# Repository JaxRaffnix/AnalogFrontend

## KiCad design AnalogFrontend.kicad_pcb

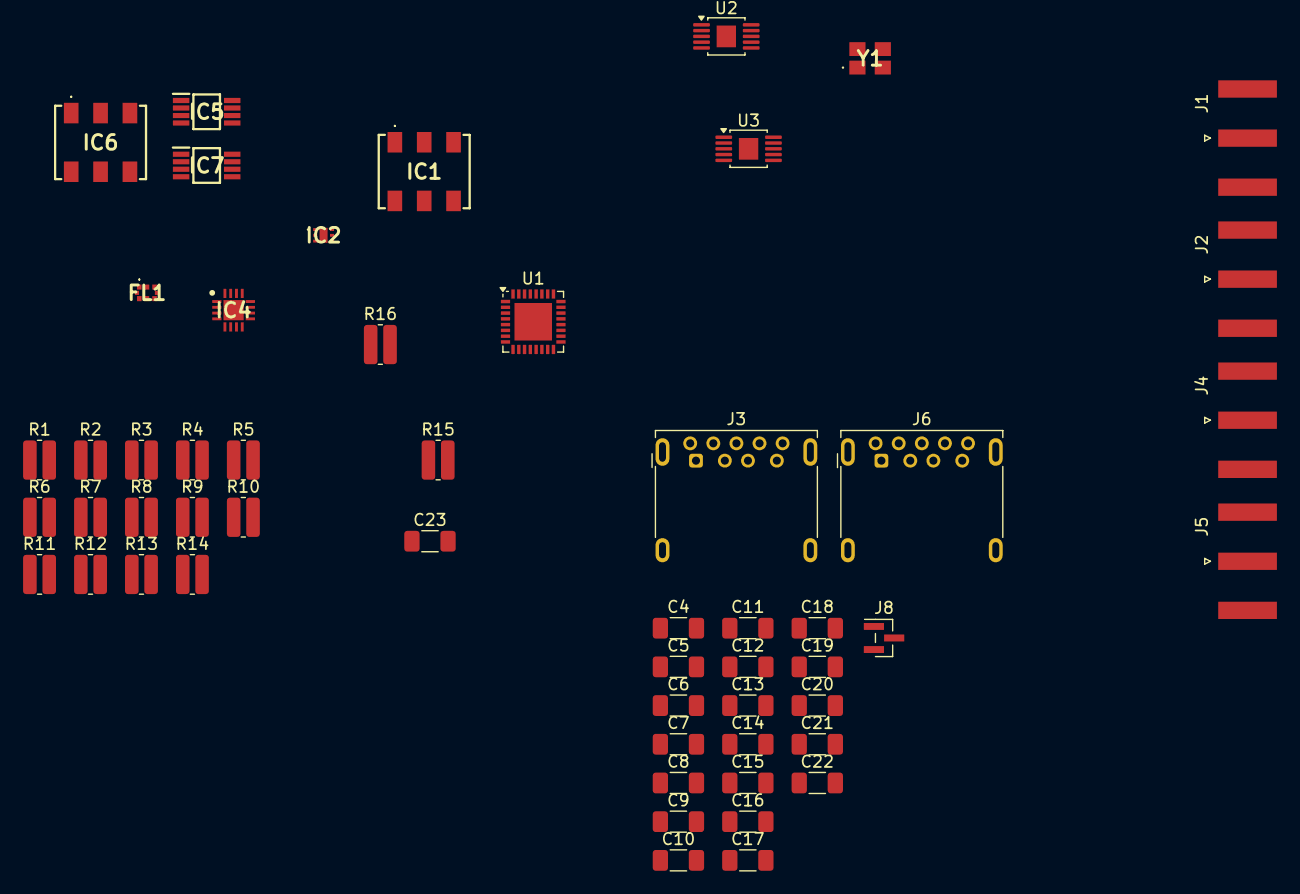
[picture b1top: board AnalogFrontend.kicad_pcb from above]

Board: 2 copper layers, 54 parts (0 on the bottom side), 33 nets, no tracks yet.

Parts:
C4, C5, C6, C21, C22, C23: 4.7muF; C_1206_3216Metric_Pad1.33x1.80mm_HandSolder
C7, C10, C12: 10pF; C_1206_3216Metric_Pad1.33x1.80mm_HandSolder
C8, C9, C11: 0.1muF; C_1206_3216Metric_Pad1.33x1.80mm_HandSolder
C13: 2.7mu; C_1206_3216Metric_Pad1.33x1.80mm_HandSolder
C14: 39n; C_1206_3216Metric_Pad1.33x1.80mm_HandSolder
C15: 1.2mu; C_1206_3216Metric_Pad1.33x1.80mm_HandSolder
C16, C17, C18, C19: 1n; C_1206_3216Metric_Pad1.33x1.80mm_HandSolder
C20: 10n; C_1206_3216Metric_Pad1.33x1.80mm_HandSolder
FL1: LLP.2500.X.B.30; LLP2500XB30
IC1, IC6: RMS-30+; RMS30
IC2: SKY65405-21; SKY6540521
IC4: SE2576L-R; QFN50P300X300X90-17N-D
IC5, IC7: MAX2752EUA+; SOP65P490X110-8N
J1, J2, J4, J5: Conn_Coaxial_x2; SMA_Amphenol_132289_EdgeMount
J3, J6: USB_A; USB3_A_Molex_48393-001
J8: Conn_01x03_Pin; PinHeader_1x03_P1.00mm_Vertical_SMD_Pin1Left
R1, R2: R; R_0612_1632Metric_Pad1.18x3.40mm_HandSolder
R3, R14: 200k; R_0612_1632Metric_Pad1.18x3.40mm_HandSolder
R4, R13: 33.2k; R_0612_1632Metric_Pad1.18x3.40mm_HandSolder
R5, R12: 499; R_0612_1632Metric_Pad1.18x3.40mm_HandSolder
R6, R15: 453k; R_0612_1632Metric_Pad1.18x3.40mm_HandSolder
R7, R16: 49.9k; R_0612_1632Metric_Pad1.18x3.40mm_HandSolder
R8: 4.7k; R_0612_1632Metric_Pad1.18x3.40mm_HandSolder
R9: 360; R_0612_1632Metric_Pad1.18x3.40mm_HandSolder
R10: 680; R_0612_1632Metric_Pad1.18x3.40mm_HandSolder
R11: 51; R_0612_1632Metric_Pad1.18x3.40mm_HandSolder
U1: ADF4351; LFCSP-32-1EP_5x5mm_P0.5mm_EP3.25x3.25mm
U2, U3: LT3042xMSE; MSOP-10-1EP_3x3mm_P0.5mm_EP1.68x1.88mm
Y1: ATX-H11-F-25.000MHz-F25-T; ATXH11F25000MHzF25T

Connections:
+3.3V: C6.1, C20.1, C23.1, R6.2, R15.2, U1.4 (CE), U1.6 (Vp), U1.10 (AVDD), U1.26 (PDB_RF), U1.28 (DVDD), U1.32 (SDVDD), U2.9 (OUTS), U2.10 (OUT), U3.9 (OUTS), U3.10 (OUT), Y1.1 (~INH), Y1.4 (VDD)
+5V: C4.1, C21.1, IC2.1 (V_ENABLE_), IC2.6 (VCC), IC4.2 (EN), IC4.4 (VCCO), IC4.13 (VCC2), IC4.15 (VCC1), IC5.4 (~SHDN), IC5.5 (VCC1), IC5.6 (VCC2), IC7.4 (~SHDN), IC7.5 (VCC1), IC7.6 (VCC2), J3.1 (VBUS), J6.1 (VBUS), R3.1, R14.1, U2.1 (IN), U2.2 (IN), U2.3 (EN/UV), U3.1 (IN), U3.2 (IN), U3.3 (EN/UV)
/Oscillator TX Output: C17.2, IC1.1 (LO)
GND: C4.2, C5.2, C6.2, C7.2, C8.2, C9.2, C10.2, C11.2, C12.2, C13.2, C15.2, C20.2, C21.2, C22.2, C23.2, FL1.1, FL1.2, FL1.3, FL1.6, FL1.7, FL1.8, IC1.2 (GROUND_1), IC1.3 (GROUND_2), IC1.6 (GROUND_3), IC2.2 (GND_1), IC2.5 (GND_2), IC2.7 (GND_3), IC4.3 (GND_1), IC4.5 (GND_2), IC4.6 (GND_3), IC4.8 (NC_1), IC4.9 (GND_4), IC4.12 (GND_5), IC4.16 (GND_6), IC4.17 (EP_(GND)), IC5.3 (GND_1), IC5.8 (GND_2), IC6.2 (GROUND_1), IC6.3 (GROUND_2), IC6.6 (GROUND_3), IC7.3 (GND_1), IC7.8 (GND_2), J3.4 (GND), J3.SH (Shield), J6.4 (GND), J6.SH (Shield), R1.2, R2.2, R4.1, R5.1, R7.1, R8.2, R9.1, R11.2, R12.1, R13.1, R16.1, U1.8 (CPGND), U1.9 (AGND), U1.11 (AGNDVCO), U1.18 (AGNDVCO), U1.21 (AGNDVCO), U1.27 (DGND), U2.8 (GND), U2.11 (GND), U3.8 (GND), U3.11 (GND), Y1.2 (GND)
unnamed: C14.2, R9.2
unnamed: C18.2, C19.1, R11.1
unnamed: IC1.5 (IF), J1.1 (IN1_1)
unnamed: FL1.4, IC1.4 (RF)
unnamed: IC2.3 (RF_IN), J4.2 (IN2_2)
unnamed: IC2.4 (RF_OUT), IC6.4 (RF)
unnamed: IC4.10 (RFOUT), IC4.11 (RF_OUT), J2.1 (IN1_1)
unnamed: FL1.5, IC4.1 (RF_IN)
unnamed: IC6.5 (IF), J5.2 (IN2_2)
unnamed: J8.1, U1.1 (CLK)
unnamed: J8.2, U1.2 (DATA)
unnamed: J8.3, U1.3 (LE)
unnamed: C13.1, C14.1, R10.2, U1.7 (CPout)
unnamed: C18.1, U1.29 (REFIN)
unnamed: C17.1, U1.12 (RF_OUT_A+)
unnamed: C16.1, U1.13 (RF_OUT_A-)
unnamed: C7.1, C8.1, R8.1, U1.22 (RSET), U1.24 (VREF)
unnamed: C11.1, C12.1, U1.19 (TEMP)
unnamed: C9.1, C10.1, U1.23 (VCOM)
unnamed: C15.1, R10.1, U1.20 (VTUNE)
unnamed: R5.2, U2.5 (ILIM)
unnamed: R3.2, U2.4 (PG)
unnamed: R6.1, R7.2, U2.6 (PGFB)
unnamed: C5.1, R4.2, U2.7 (SET)
unnamed: R12.2, U3.5 (ILIM)
unnamed: R14.2, U3.4 (PG)
unnamed: R15.1, R16.2, U3.6 (PGFB)
unnamed: C22.1, R13.2, U3.7 (SET)
unnamed: C19.2, Y1.3 (OUTPUT)

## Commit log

2026-05-07 inital commit
2026-05-08 update schematic
2026-05-28 updatged schematics
2026-05-28 updated schematics
2026-05-28 updated lockfile
2026-05-28 updated merge
2026-05-28 added new schematics
